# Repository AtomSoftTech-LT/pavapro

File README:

github repo for project pavapro
http://hackaday.io/project/3511-pavapro-portable-avr-programmer

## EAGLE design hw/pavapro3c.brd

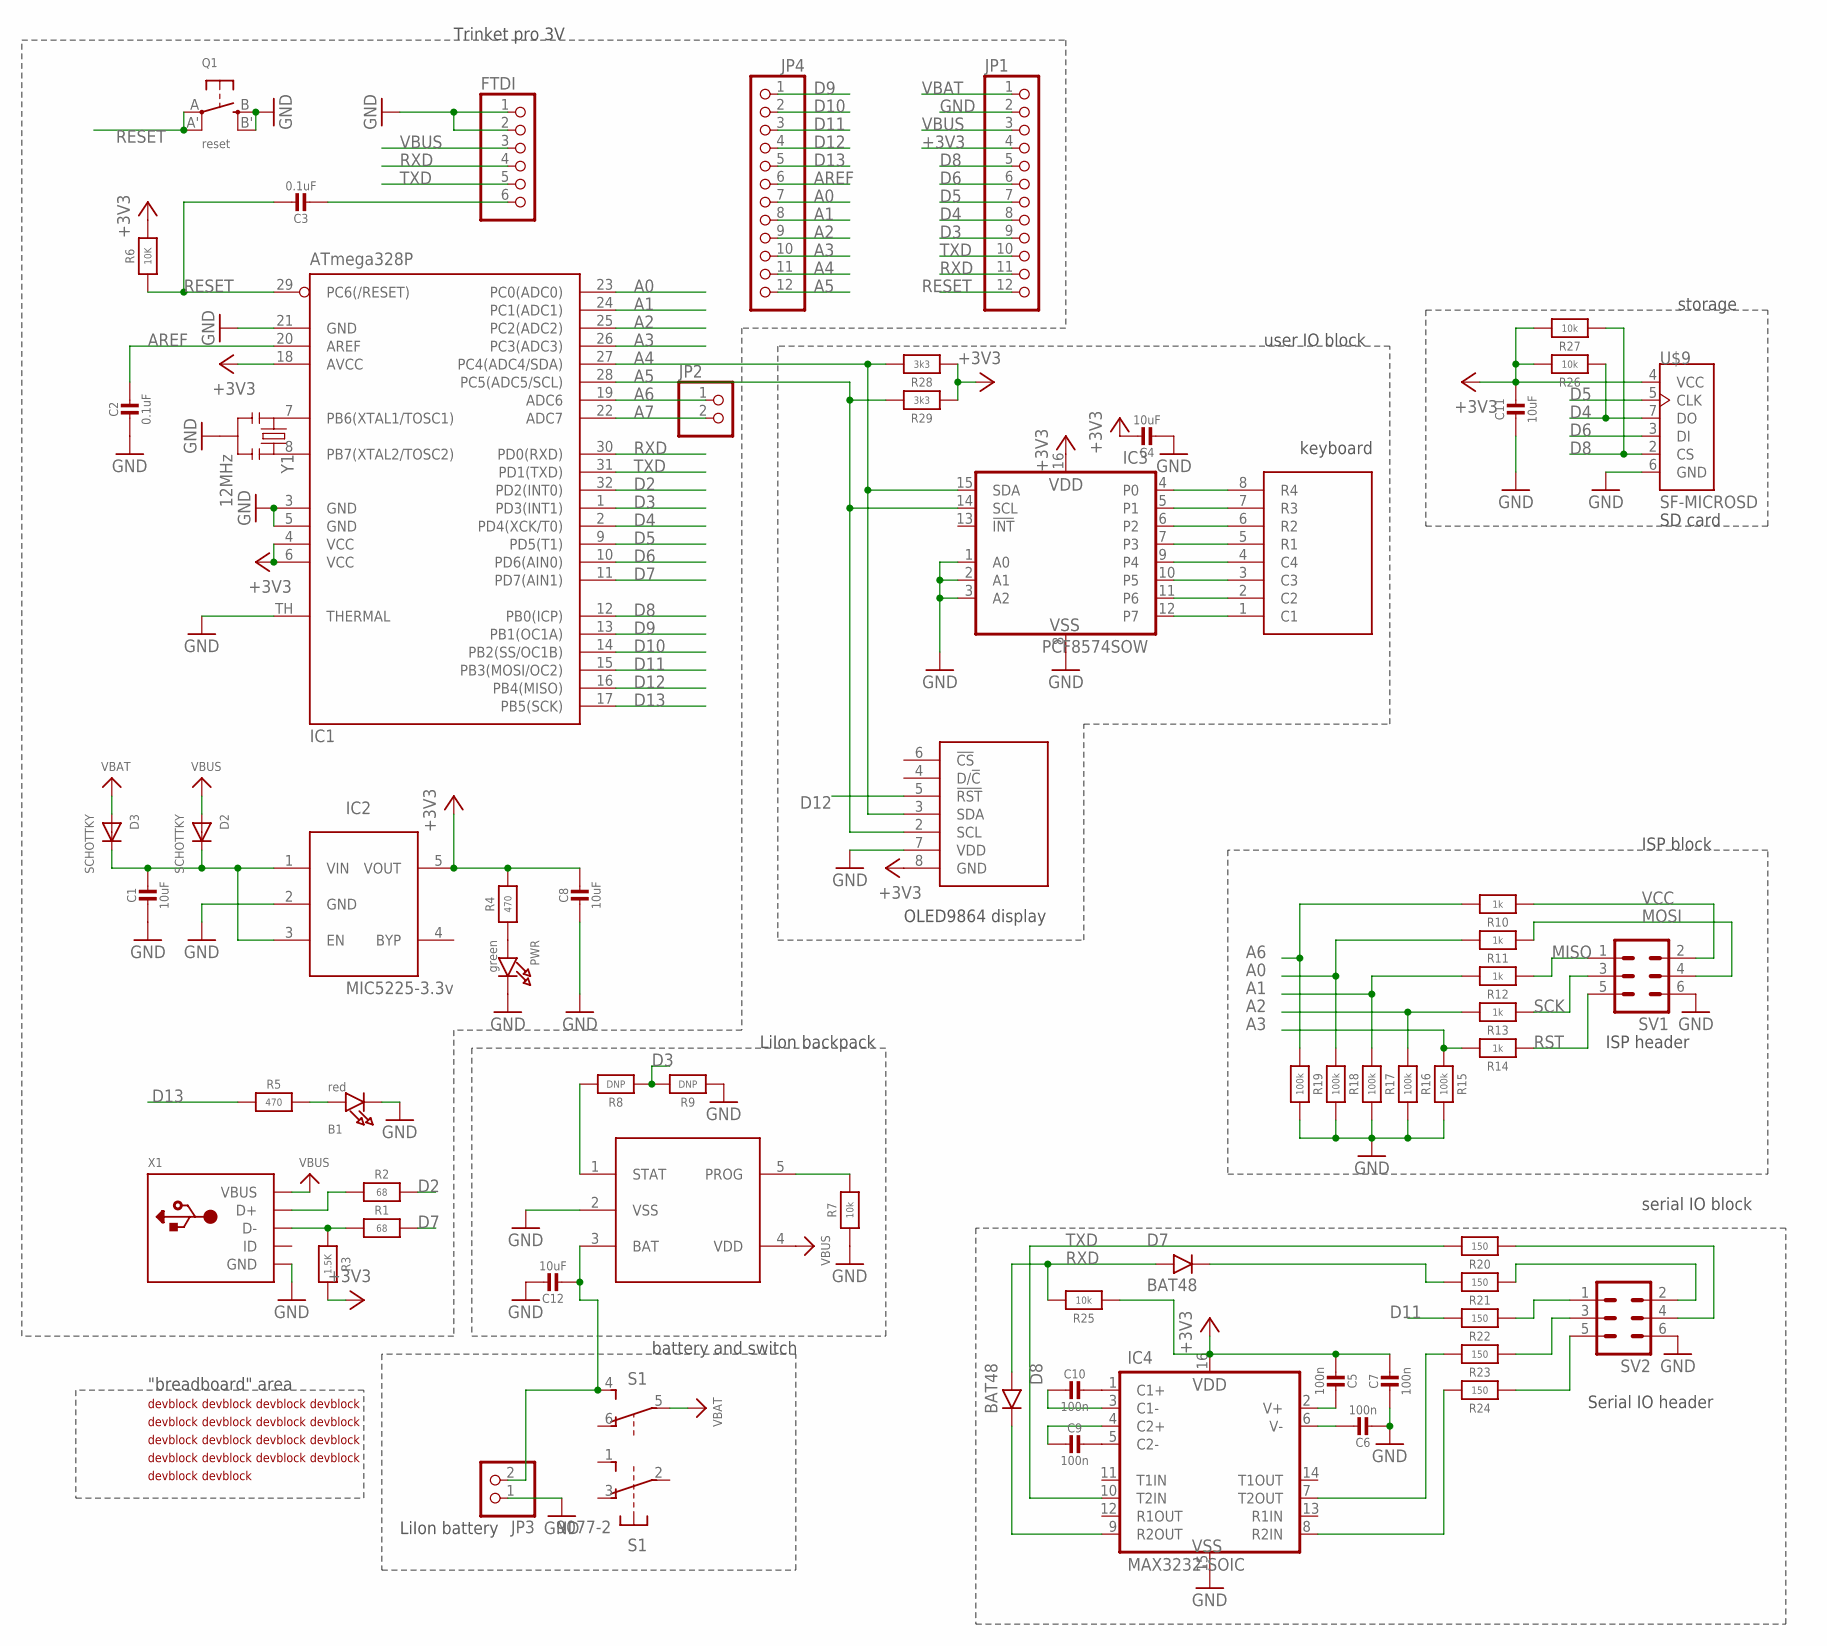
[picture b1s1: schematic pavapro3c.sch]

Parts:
B1: red; CHIPLED_0805_NOOUTLINE
C1, C4, C8, C11, C12: 10uF; 0805-NO
C2: 0.1uF; _0805MP
C3: 0.1uF; 0805-NO
C5, C6, C7, C9, C10: 100n; 0805-NO
D2, D3: SCHOTTKY; ADAFRUIT_SOD-123FL
D7, D8: BAT48; SOD-80
FTDI: ADAFRUIT_PINHD-1X6CB; ADAFRUIT_1X06-CLEANBIG
IC1: ATmega328P; MLF32-TH
IC2: MIC5225-3.3v; SOT23-5L
IC3: PCF8574SOW; SO-16DW
IC4: MAX3232-SOIC; SO-16
JP1, JP4: ADAFRUIT_PINHD-1X12-CB; ADAFRUIT_1X12-CB
JP2: HEADER-1X2ROUND; 1X02_ROUND
JP3: PINHD-1X02_2.54-90°; 1X02/90
PWR: green; CHIPLED_0805_NOOUTLINE
Q1: reset; BTN_KMR2_4.6X2.8
R1, R2: 68; 0603-NO
R3: 1.5K; 0603-NO
R4, R5: 470; 0603-NO
R6: 10K; 0805-NO
R7, R25, R26, R27: 10k; _0805
R8, R9: DNP; _0805
R10, R11, R12, R13, R14: 1k; _0805
R15, R16, R17, R18, R19: 100k; _0805
R20, R21, R22, R23, R24: 150; _0805
R28, R29: 3k3; _0805
S1: 9077-2
SV1, SV2: ML6
U$5: DISP_OLED_2864; OLED2864
U$6: MCP73831; SOT23-5
U$7: KB1604
U$9: SF-MICROSD; MICROSD
U$10, U$11, U$12, U$13, U$14, U$15, U$16, U$17, U$18, U$19, U$20, U$21, U$22, U$23, U$24, U$25, U$26, U$27: DEVBLOCK_1_16
X1: MICROBUILDER_USBMICRO_20329; MICROBUILDER_4UCONN_20329
Y1: 12MHz; RESONATOR-SMD

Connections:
+3V3: C4.1, C5.2, C7.1, C8.1, C11.1, IC1.4 (VCC), IC1.6 (VCC), IC1.18 (AVCC), IC2.5 (VOUT), IC3.16 (VDD), IC4.16 (VDD), JP1.4, R3.2, R4.2, R6.2, R25.2, R26.1, R27.1, R28.2, R29.2, U$5.8 (GND), U$9.4 (VCC)
A0: IC1.23 (PC0(ADC0)), JP4.7, R11.1, R18.2
A1: IC1.24 (PC1(ADC1)), JP4.8, R12.1, R17.2
A2: IC1.25 (PC2(ADC2)), JP4.9, R13.1, R16.2
A3: IC1.26 (PC3(ADC3)), JP4.10, R14.1, R15.2
A4: IC1.27 (PC4(ADC4/SDA)), IC3.15 (SDA), JP4.11, R28.1, U$5.3 (SDA)
A5: IC1.28 (PC5(ADC5/SCL)), IC3.14 (SCL), JP4.12, R29.1, U$5.2 (SCL)
A6: IC1.19 (ADC6), JP2.1, R10.1, R19.2
A7: IC1.22 (ADC7), JP2.2
AREF: C2.1, IC1.20 (AREF), JP4.6
D2: IC1.32 (PD2(INT0)), R2.2
D3: IC1.1 (PD3(INT1)), JP1.9, R8.2, R9.1
D4: IC1.2 (PD4(XCK/T0)), JP1.8, R26.2, U$9.7 (DO)
D5: IC1.9 (PD5(T1)), JP1.7, U$9.5 (CLK)
D6: IC1.10 (PD6(AIN0)), JP1.6, U$9.3 (DI)
D7: IC1.11 (PD7(AIN1)), R1.2
D8: IC1.12 (PB0(ICP)), JP1.5, R27.2, U$9.2 (CS)
D9: IC1.13 (PB1(OC1A)), JP4.1
D10: IC1.14 (PB2(SS/OC1B)), JP4.2
D11: IC1.15 (PB3(MOSI/OC2)), JP4.3, R22.1
D12: IC1.16 (PB4(MISO)), JP4.4, U$5.5 (!RST)
D13: IC1.17 (PB5(SCK)), JP4.5, R5.2
D+: R2.1, X1.D+
D-: R1.1, R3.1, X1.D-
DTR/RTS: C3.2, FTDI.6
GND: B1.C, C1.2, C2.2, C4.2, C6.2, C7.2, C8.2, C11.2, C12.1, FTDI.1, FTDI.2, IC1.3 (GND), IC1.5 (GND), IC1.21 (GND), IC1.TH (THERMAL), IC2.2 (GND), IC3.1 (A0), IC3.2 (A1), IC3.3 (A2), IC3.8 (VSS), IC4.15 (VSS), JP1.2, JP3.1, PWR.C, Q1.B (S), Q1.B' (S1), R7.2, R9.2, R15.1, R16.1, R17.1, R18.1, R19.1, SV1.6, SV2.6, U$5.7 (VDD), U$6.2 (VSS), U$9.6 (GND), X1.BASE@1 (GND), X1.BASE@2 (GND), X1.GND, X1.SPRT@1 (GND), X1.SPRT@2 (GND), X1.SPRT@3 (GND), X1.SPRT@4 (GND), Y1.2
MISO: R12.2, SV1.1
MOSI: R11.2, SV1.4
unnamed: B1.A, R5.1
unnamed: IC1.8 (PB7(XTAL2/TOSC2)), Y1.3
unnamed: IC1.7 (PB6(XTAL1/TOSC1)), Y1.1
unnamed: PWR.A, R4.1
unnamed: C1.1, D2.C, D3.C, IC2.1 (VIN), IC2.3 (EN)
unnamed: IC3.12 (P7), U$7.1 (C1)
unnamed: IC3.11 (P6), U$7.2 (C2)
unnamed: IC3.10 (P5), U$7.3 (C3)
unnamed: IC3.9 (P4), U$7.4 (C4)
unnamed: IC3.7 (P3), U$7.5 (R1)
unnamed: IC3.6 (P2), U$7.6 (R2)
unnamed: IC3.5 (P1), U$7.7 (R3)
unnamed: IC3.4 (P0), U$7.8 (R4)
unnamed: C12.2, JP3.2, S1.4 (S), U$6.3 (BAT)
unnamed: R7.1, U$6.5 (PROG)
unnamed: R8.1, U$6.1 (STAT)
unnamed: R20.2, SV2.4
unnamed: R21.2, SV2.2
unnamed: R22.2, SV2.1
unnamed: R23.2, SV2.3
unnamed: R24.2, SV2.5
unnamed: IC4.7 (T2OUT), R23.1
unnamed: D7.K, R21.1
unnamed: D8.K, IC4.9 (R2OUT)
unnamed: C6.1, IC4.6 (V-)
unnamed: C5.1, IC4.2 (V+)
unnamed: C9.1, IC4.5 (C2-)
unnamed: C10.1, IC4.1 (C1+)
unnamed: C10.2, IC4.3 (C1-)
unnamed: C9.2, IC4.4 (C2+)
unnamed: IC4.8 (R2IN), R24.1
RESET: C3.1, IC1.29 (PC6(/RESET)), JP1.12, Q1.A, Q1.A' (P1), R6.1
RST: R14.2, SV1.5
RXD: D7.A, D8.A, FTDI.4, IC1.30 (PD0(RXD)), JP1.11, R25.1
SCK: R13.2, SV1.3
TXD: FTDI.5, IC1.31 (PD1(TXD)), IC4.10 (T2IN), JP1.10, R20.1
VBAT: D3.A, JP1.1, S1.5
VBUS: D2.A, FTDI.3, JP1.3, U$6.4 (VDD), X1.VBUS
VCC: R10.2, SV1.2

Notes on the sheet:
Trinket pro 3V
LiIon backpack
LiIon battery
ISP header
Serial IO header
SD card
keyboard
OLED9864 display
serial IO block
ISP block
user IO block
storage
battery and switch
"breadboard" area

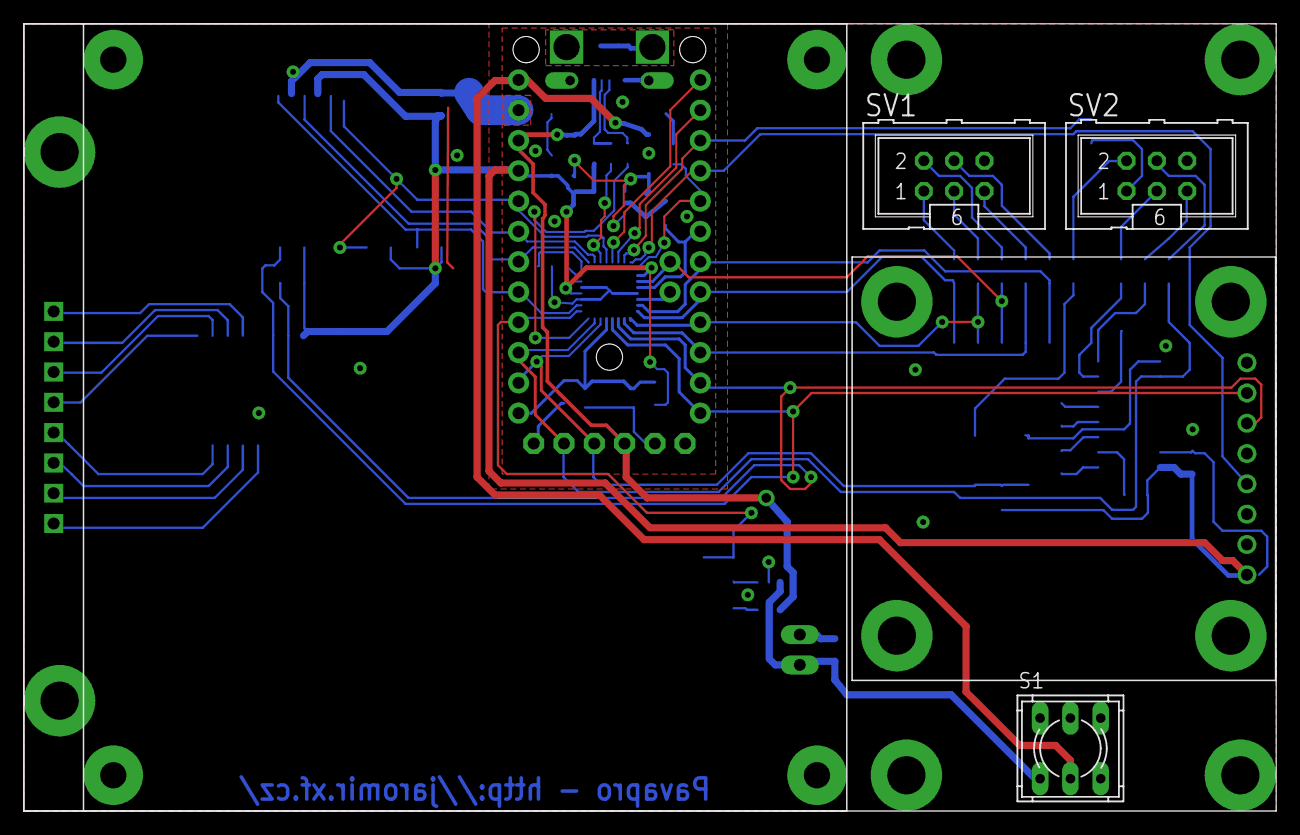
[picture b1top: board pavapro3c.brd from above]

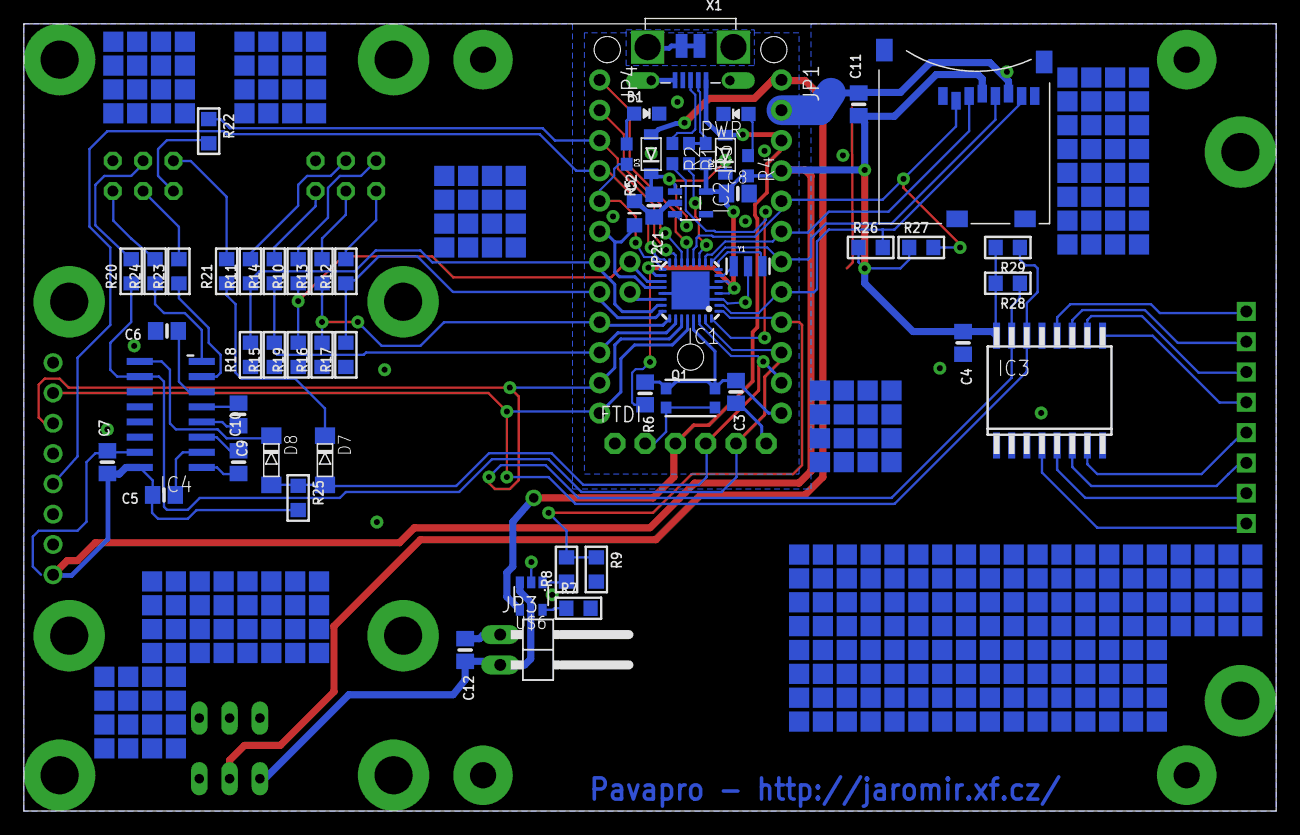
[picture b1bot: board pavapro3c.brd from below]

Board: 2 copper layers, 105.0 x 66.0 mm, 84 parts (79 on the bottom side), 67 nets.

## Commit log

2014-12-03 :neckbeard: Added .gitattributes
2014-12-03 first, testing bootloader for 12MHz arduino
    bootloader for 12MHz arduino
2014-12-26 test fw 1
2015-01-03 ver 2
2015-01-03 ver 3

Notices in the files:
parts and their libraries:
microbuilder: This work is placed in the public domain, and may be freely used for commercial and non-commercial work with the following conditions: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
SparkFun: Licensing: CC v3.0 Share-Alike You are welcome to use this library for commercial purposes.
